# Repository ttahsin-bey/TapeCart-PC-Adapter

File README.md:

# TapeCart PC-Adapter
USB-Adapter to connect your TapeCart directly to your PC

Current Design:

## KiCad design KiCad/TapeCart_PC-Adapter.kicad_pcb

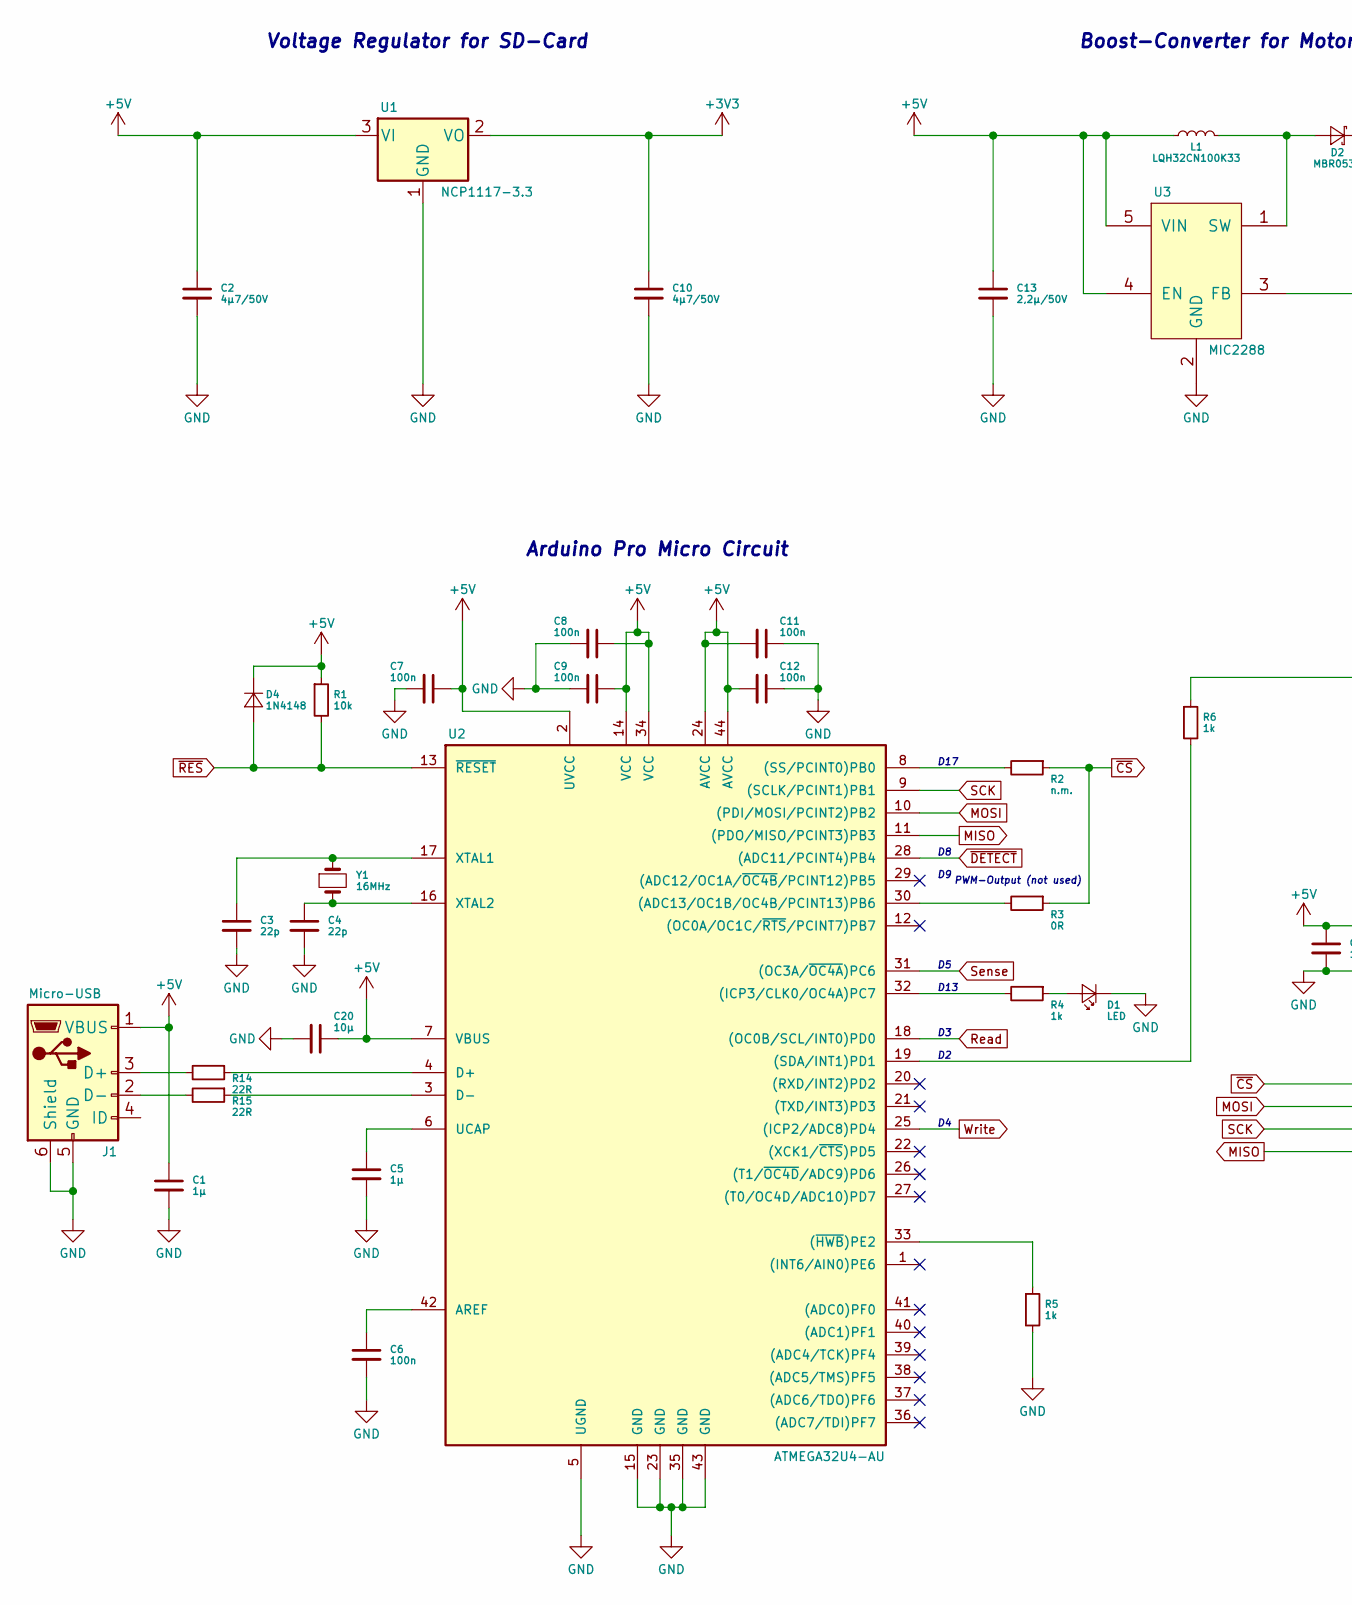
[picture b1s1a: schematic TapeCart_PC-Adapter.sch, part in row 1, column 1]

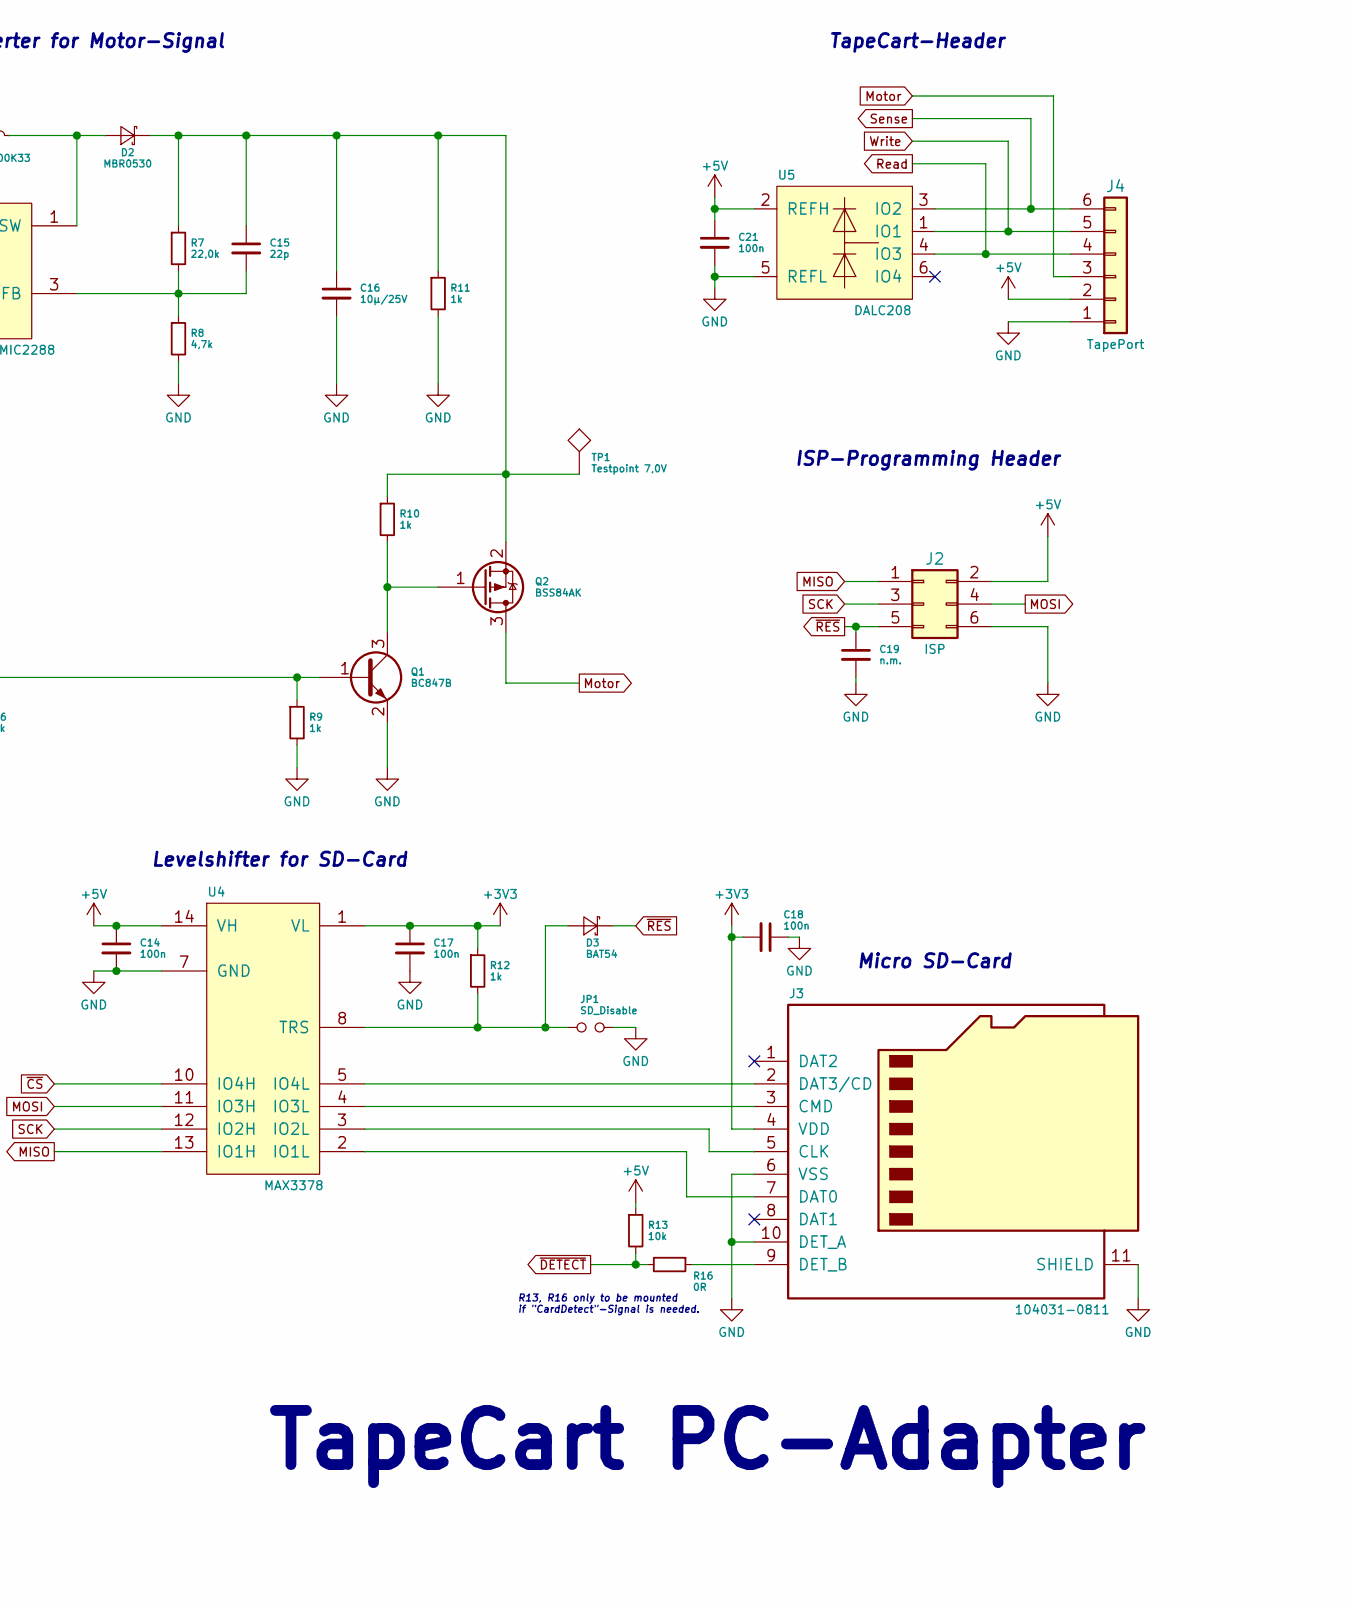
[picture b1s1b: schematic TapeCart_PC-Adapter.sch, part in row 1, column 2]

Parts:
C1: 1µ; TTB_C1206
C2, C10: 4µ7/50V; TTB_C1206
C3, C4: 22p; TTB_C0603wide
C5: 1µ; TTB_C0805
C6, C7, C8, C9, C11, C12, C14, C17, C18, C21: 100n; TTB_C0603
C13: 2,2µ/50V; TTB_C1206
C15: 22p; TTB_C0603
C16: 10µ/25V; TTB_C1206
C19: n.m.; TTB_C0603
C20: 10µ; TTB_C0805
D1: LED; TTB_LED0805
D2: MBR0530; TTB_D_SOD-123; Digikey MBR0530CT-ND
D3: BAT54; TTB_SOT23; Digikey BAT54FSCT-ND
D4: 1N4148; TTB_D0603
J1: Micro-USB; TTB_USB-B_Micro_Würth
J2: ISP; TTB_Pinhead_2x3
J3: 104031-0811; TTB_MicroSD_1040310811; Digikey WM6357CT-ND
J4: TapePort; TTB_C64_Tapeport_PCB
JP1: SD_Disable; TTB_Pinhead_1x2
L1: LQH32CN100K33; TTB_L_MURATA-LQH32; Digikey 490-6614-1-ND
Q1: BC847B; TTB_SOT23; Digikey BC847BLT3GOSCT-ND
Q2: BSS84AK; TTB_SOT23; Digikey BSS84CT-ND
R1, R13: 10k; TTB_R0603
R2: n.m.; TTB_R0603
R3, R16: 0R; TTB_R0603
R4, R5, R6, R9, R10, R11, R12: 1k; TTB_R0603
R7: 22,0k; TTB_R0603
R8: 4,7k; TTB_R0603
R14, R15: 22R; TTB_R0603
TP1: Testpoint 7,0V; Measurement_Point_Round-SMD-Pad_Small
U1: NCP1117-3.3; SOT-223-3Lead_TabPin2
U2: ATMEGA32U4-AU; TQFP-44_10x10mm_Pitch0.8mm
U3: MIC2288; SOT-23-5_HandSoldering; Digikey 576-1729-1-ND
U4: MAX3378; TSSOP-14_4.4x5mm_Pitch0.65mm; Digikey MAX3378EEUD+-ND
U5: DALC208; TTB_SOT23-6L
Y1: 16MHz; TTB_7A

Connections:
+3V3: C10.1, C17.1, C18.2, J3.4 (VDD), R12.1, U1.2 (VO), U4.1 (VL)
+5V: C1.1, C2.1, C7.1, C8.1, C9.1, C11.2, C12.2, C13.1, C14.1, C20.1, C21.1, D4.1 (K), J1.1 (VBUS), J2.2, J4.2, L1.1, R1.1, R13.1, U1.3 (VI), U2.2 (UVCC), U2.7 (VBUS), U2.14 (VCC), U2.24 (AVCC), U2.34 (VCC), U2.44 (AVCC), U3.4 (EN), U3.5 (VIN), U4.14 (VH), U5.2 (REFH)
GND: C1.2, C2.2, C3.2, C4.2, C5.2, C6.2, C7.2, C8.2, C9.2, C10.2, C11.1, C12.1, C13.2, C14.2, C16.2, C17.2, C18.1, C19.2, C20.2, C21.2, D1.1 (K), J1.5 (GND), J1.6 (Shield), J2.6, J3.6 (VSS), J3.10 (DET_A), J3.11 (SHIELD), J4.1, JP1.2, Q1.2 (E), R5.2, R8.2, R9.2, R11.2, U1.1 (GND), U2.5 (UGND), U2.15 (GND), U2.23 (GND), U2.35 (GND), U2.43 (GND), U3.2 (GND), U4.7 (GND), U5.5 (REFL)
MISO: J2.1, U2.11 ((PDO/MISO/PCINT3)PB3), U4.13 (IO1H)
MOSI: J2.4, U2.10 ((PDI/MOSI/PCINT2)PB2), U4.11 (IO3H)
Motor: J4.3, Q2.3 (D)
unnamed: C3.1, U2.17 (XTAL1), Y1.1
unnamed: C4.1, U2.16 (XTAL2), Y1.2
unnamed: C5.1, U2.6 (UCAP)
unnamed: C6.1, U2.42 (AREF)
unnamed: C15.1, C16.1, D2.1 (K), Q2.2 (S), R7.1, R10.1, R11.1, TP1.1
unnamed: C15.2, R7.2, R8.1, U3.3 (FB)
unnamed: D1.2 (A), R4.1
unnamed: D2.2 (A), L1.2, U3.1 (SW)
unnamed: D3.2 (A), JP1.1, R12.2, U4.8 (TRS)
unnamed: J1.2 (D-), R15.2
unnamed: J1.3 (D+), R14.2
unnamed: J3.2 (DAT3/CD), U4.5 (IO4L)
unnamed: J3.3 (CMD), U4.4 (IO3L)
unnamed: J3.5 (CLK), U4.3 (IO2L)
unnamed: J3.7 (DAT0), U4.2 (IO1L)
unnamed: J3.9 (DET_B), R16.1
unnamed: Q1.1 (B), R6.1, R9.1
unnamed: Q1.3 (C), Q2.1 (G), R10.2
unnamed: R2.2, U2.8 ((SS/PCINT0)PB0)
unnamed: R3.2, U2.30 ((ADC13/OC1B/OC4B/PCINT13)PB6)
unnamed: R4.2, U2.32 ((ICP3/CLK0/OC4A)PC7)
unnamed: R5.1, U2.33 ((~HWB~)PE2)
unnamed: R6.2, U2.19 ((SDA/INT1)PD1)
unnamed: R14.1, U2.4 (D+)
unnamed: R15.1, U2.3 (D-)
Read: J4.4, U2.18 ((OC0B/SCL/INT0)PD0), U5.4 (IO3)
SCK: J2.3, U2.9 ((SCLK/PCINT1)PB1), U4.12 (IO2H)
Sense: J4.6, U2.31 ((OC3A/~OC4A~)PC6), U5.3 (IO2)
Write: J4.5, U2.25 ((ICP2/ADC8)PD4), U5.1 (IO1)
~CS: R2.1, R3.1, U4.10 (IO4H)
~DETECT: R13.2, R16.2, U2.28 ((ADC11/PCINT4)PB4)
~RES: C19.1, D3.1 (K), D4.2 (A), J2.5, R1.2, U2.13 (~RESET~)

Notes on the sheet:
TapeCart PC-Adapter
Voltage Regulator for SD-Card
Boost-Converter for Motor-Signal
ISP-Programming Header
Arduino Pro Micro Circuit
Levelshifter for SD-Card
TapeCart-Header
Micro SD-Card
D13
D17
PWM-Output (not used)
R13, R16 only to be mounted if "CardDetect"-Signal is needed.

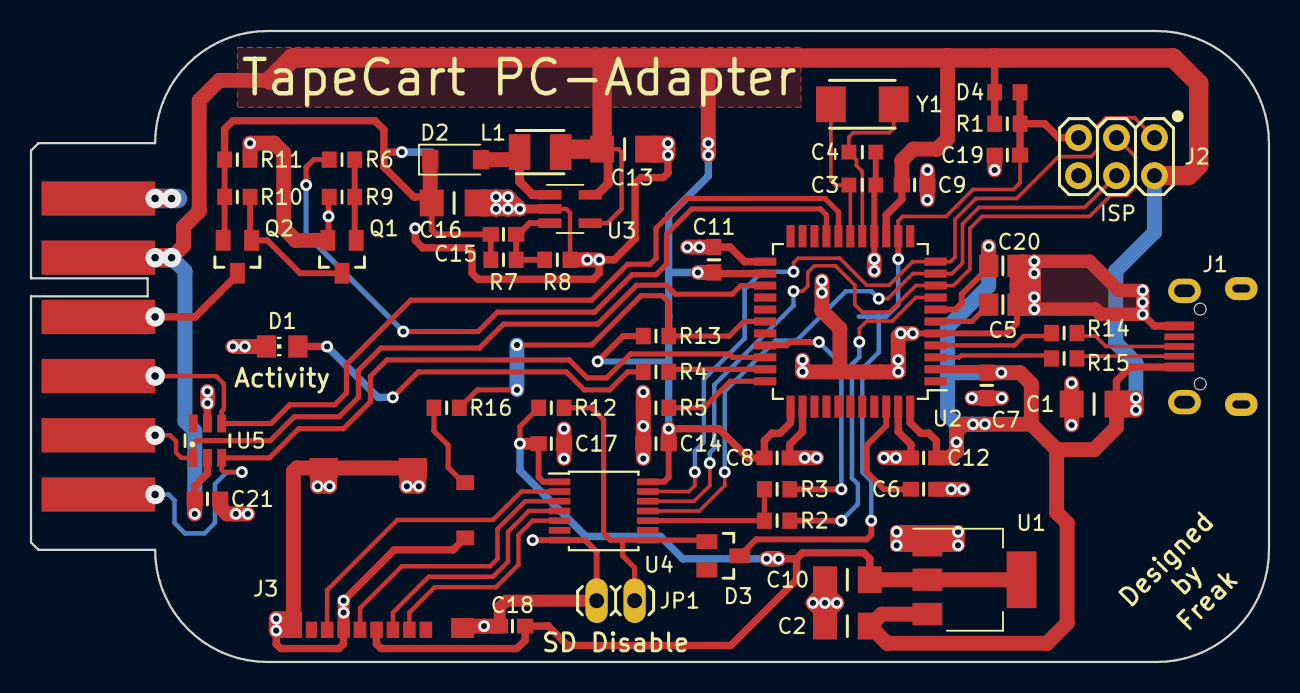
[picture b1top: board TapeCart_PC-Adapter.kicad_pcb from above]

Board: 2 copper layers, 82.8 x 42.2 mm, 56 parts (1 on the bottom side), 38 nets.

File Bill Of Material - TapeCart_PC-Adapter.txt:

Ref	Product		Package	Value			Distri	Order-Code

R1	Resistor	0603	10k, 1%			Mouser	603-RC0603FR-0710KL
R2   --	Resistor	0603	0R, 1%			Mouser	603-RC0603JR-070RL
R3	Resistor	0603	0R, 1%			Mouser	603-RC0603JR-070RL
R4	Resistor	0603	1k0, 1%			Mouser	603-RC0603FR-071KL
R5	Resistor	0603	1k0, 1%			Mouser	603-RC0603FR-071KL
R6	Resistor	0603	1k0, 1%			Mouser	603-RC0603FR-071KL
R7	Resistor	0603	22k, 1%			Mouser	603-RC0603FR-0722KL
R8	Resistor	0603	4k7, 1%			Mouser	603-RC0603FR-074K7L
R9	Resistor	0603	1k0, 1%			Mouser	603-RC0603FR-071KL
R10	Resistor	0603	1k0, 1%			Mouser	603-RC0603FR-071KL
R11	Resistor	0603	1k0, 1%			Mouser	603-RC0603FR-071KL
R12	Resistor	0603	1k0, 1%			Mouser	603-RC0603FR-071KL
R13	Resistor	0603	10k, 1%			Mouser	603-RC0603FR-0710KL
R14	Resistor	0603	22R, 1%			Mouser	603-RC0603FR-0722RL
R15	Resistor	0603	22R, 1%			Mouser	603-RC0603FR-0722RL

C1	Capacitor	1206	1µF/50V, X7R, MLCC	Mouser
C2	Capacitor	1206	4µ7F/50V, X7R, MLCC	Mouser
C3	Capacitor	0603	22pF/25V, NP0, MLCC	Mouser	603-CC603JRNPO8BN220
C4	Capacitor	0603	22pF/25V, NP0, MLCC	Mouser	603-CC603JRNPO8BN220
C5	Capacitor	0805	1µF/25V, X7R, MLCC	Mouser
C6	Capacitor	0603	100nF/50V, X7R, MLCC	Mouser	603-CC603KRX7R9BB104
C7	Capacitor	0603	100nF/50V, X7R, MLCC	Mouser	603-CC603KRX7R9BB104
C8	Capacitor	0603	100nF/50V, X7R, MLCC	Mouser	603-CC603KRX7R9BB104
C9	Capacitor	0603	100nF/50V, X7R, MLCC	Mouser	603-CC603KRX7R9BB104
C10	Capacitor	1206	4µ7F/50V, X7R, MLCC	Mouser
C11	Capacitor	0603	100nF/50V, X7R, MLCC	Mouser	603-CC603KRX7R9BB104
C12	Capacitor	0603	100nF/50V, X7R, MLCC	Mouser	603-CC603KRX7R9BB104
C13	Capacitor	1206	2µ2F/50V
C14	Capacitor	0603	100nF/50V, X7R, MLCC	Mouser	603-CC603KRX7R9BB104
C15  --	Capacitor	0603	22pF/50V, NP0, MLCC	Mouser	603-CC603JRNPO9BN220
C16	Capacitor	1206	10µ/25V, X7R, MLCC	Mouser
C17	Capacitor	0603	100nF/50V, X7R, MLCC	Mouser	603-CC603KRX7R9BB104
C18	Capacitor	0603	100nF/50V, X7R, MLCC	Mouser	603-CC603KRX7R9BB104
C19  --	Capacitor	0603	47nF/50V, X7R, MLCC	Mouser	603-C0603KRX7R9BB473
C20	Capacitor	0805	10µF/25V

D1	LED Rot		0805	APT2012LSECK/J3-PRV	Mouser	604-APT2012LSECKJ3RV
D2	Diode			MBR0530
D3	Diode		SOT23-3	BAT54			Mouser	863-BAT54CLT3G
D4	Diode			TS4148

L1	Inductor	n.a.	LQH32CN100K33

J1	USB-Connector	n.a.	Würth 629105150521	Mouser	710-629105150521
J2   --	ISP-Connector	n.a.	2*3 Pinheader 2,54mm	Reichlt	MPE 087-2-006
J3	microSD-Conn.	n.a.	Molex 104031-0811	Mouser	538-104031-0811

JP1  --	Jumper		n.a.	1*2 Pinheader 2,54mm	Reichlt	MPE 087-1-002

Q1	Transistor	SOT23-3	BC847B,215 (NXP)	Mouser	771-BC847B-T/R
Q2	Transistor	SOT23-3	BSS84,215 (NXP)		Mouser	771-BSS84-T/R

U1	IC (U-Reg)	SOT223	TLV1117-3.3		Mouser	595-TLV1117-33CDCYR
U2	IC (CPU)	TQFP44	ATMEGA32U4-AU		Mouser	556-ATMEGA32U4-AU
U3	IC		SOT23-5	MIC2288YD5-TR		Mouser	998-MIC2288YD5TR
U4	IC		TSSOP14	MAX3378EEUD+		Mouser	700-MAX3378EEUD
U5	IC			DALC208

Y1	Crystal		7A	16MHz, 18pF		Mouser	717-7A-16.000MAAJ-T

PCB	1,6mm / 2 Layers

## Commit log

2018-10-08 Circuit Diagram added
2018-10-08 KiCAD-Project added
2018-10-08 BOM added
2018-10-08 Rendering added
